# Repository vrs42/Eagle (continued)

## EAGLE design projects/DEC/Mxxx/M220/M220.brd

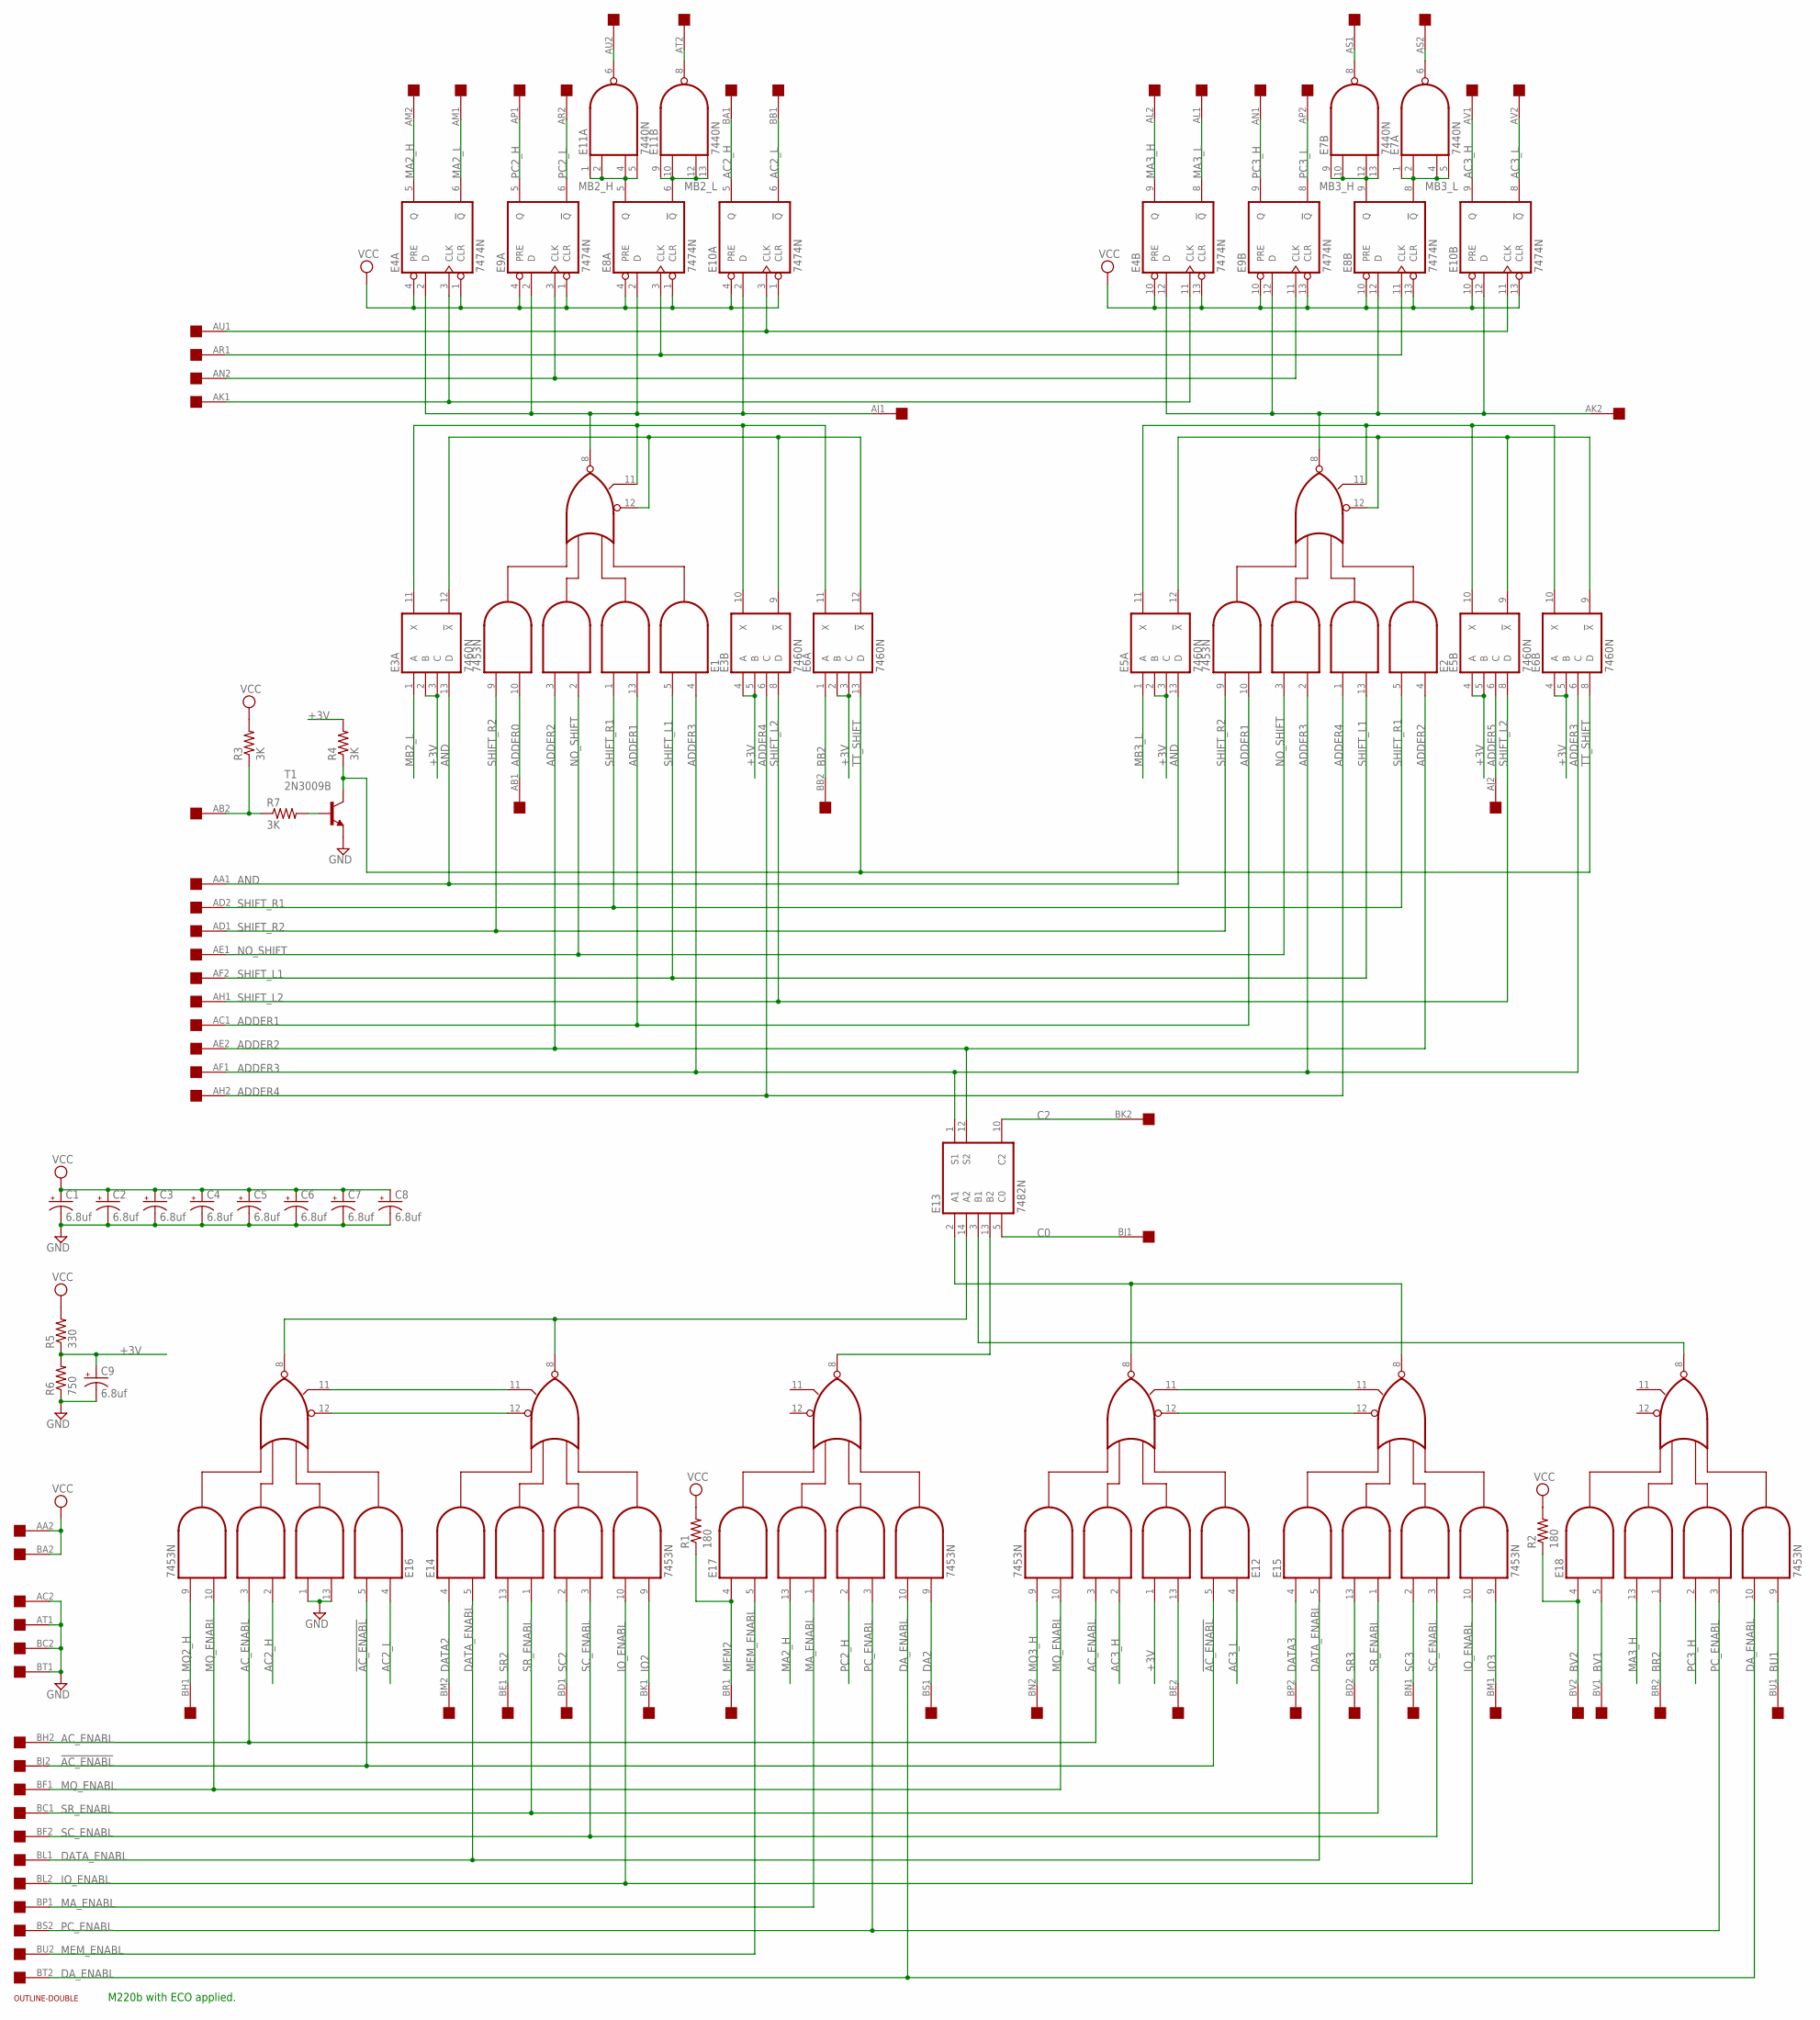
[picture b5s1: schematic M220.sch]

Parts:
C1, C2, C3, C4, C5, C6, C7, C8, C9: 6.8uf; E15-5
E1, E2, E12, E14, E15, E16, E17, E18: 7453N; DIL14
E3, E5, E6: 7460N; DIL14
E4, E8, E9, E10: 7474N; DIL14
E7, E11: 7440N; DIL14
E13: 7482N; DIL14
R1, R2: 180; 0207/10
R3, R4, R7: 3K; 0207/10
R5: 330; 0207/10
R6: 750; 0207/10
T1: 2N3009B; TO5
U$1: DOUBLE; EDGE-CON4
U$2: OUTLINE-DOUBLE; DOUBLE

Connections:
!AC_ENABL: E12.5 (I2), E16.5 (I2), U$1.BJ2
!TT_SHIFT: R3.1, R7.1, U$1.AB2
+3V: C9.+, E3.2 (B), E3.3 (C), E3.4 (A), E3.5 (B), E5.2 (B), E5.3 (C), E5.4 (A), E5.5 (B), E6.2 (B), E6.3 (C), E6.4 (A), E6.5 (B), E12.1 (I4), R4.2, R5.1, R6.2
AC2_H: E10.5 (Q), E16.2 (I5), U$1.BA1
AC2_L: E10.6 (!Q), E16.4 (I1), U$1.BB1
AC3_H: E10.9 (Q), E12.2 (I5), U$1.AV1
AC3_L: E10.8 (!Q), E12.4 (I1), U$1.AV2
AC_ENABL: E12.3 (I6), E16.3 (I6), U$1.BH2
ADDER0: E1.10 (I7), U$1.AB1
ADDER1: E1.13 (I3), E2.10 (I7), U$1.AC1
ADDER2: E1.3 (I6), E2.4 (I1), E13.12 (S2), U$1.AE2
ADDER3: E1.4 (I1), E2.2 (I5), E6.6 (C), E13.1 (S1), U$1.AF1
ADDER4: E2.1 (I4), E3.6 (C), U$1.AH2
ADDER5: E5.6 (C), U$1.AJ2
AJ1: E1.8 (O), E4.2 (D), E8.2 (D), E9.2 (D), E10.2 (D), U$1.AJ1
AK1: E4.3 (CLK), E4.11 (CLK), U$1.AK1
AK2: E2.8 (O), E4.12 (D), E8.12 (D), E9.12 (D), E10.12 (D), U$1.AK2
AN2: E9.3 (CLK), E9.11 (CLK), U$1.AN2
AND: E3.13 (D), E5.13 (D), U$1.AA1
AR1: E8.3 (CLK), E8.11 (CLK), U$1.AR1
AS1: E7.8 (O), U$1.AS1
AS2: E7.6 (O), U$1.AS2
AT2: E11.8 (O), U$1.AT2
AU1: E10.3 (CLK), E10.11 (CLK), U$1.AU1
AU2: E11.6 (O), U$1.AU2
BB2: E6.1 (A), U$1.BB2
BE2: E12.13 (I3), U$1.BE2
BR2: E18.1 (I4), U$1.BR2
BU1: E18.9 (I8), U$1.BU1
BV1: E18.5 (I2), U$1.BV1
BV2: E18.4 (I1), R2.1, U$1.BV2
C0: E13.5 (C0), U$1.BJ1
C2: E13.10 (C2), U$1.BK2
DA2: E17.9 (I8), U$1.BS1
DATA2: E14.4 (I1), U$1.BM2
DATA3: E15.4 (I1), U$1.BP2
DATA_ENABL: E14.5 (I2), E15.5 (I2), U$1.BL1
DA_ENABL: E17.10 (I7), E18.10 (I7), U$1.BT2
GND: C1.-, C2.-, C3.-, C4.-, C5.-, C6.-, C7.-, C8.-, C9.-, E1.7 (GND), E2.7 (GND), E3.7 (GND), E4.7 (GND), E5.7 (GND), E6.7 (GND), E7.7 (GND), E8.7 (GND), E9.7 (GND), E10.7 (GND), E11.7 (GND), E12.7 (GND), E13.11 (GND), E14.7 (GND), E15.7 (GND), E16.1 (I4), E16.7 (GND), E16.13 (I3), E17.7 (GND), E18.7 (GND), R6.1, T1.1 (E), U$1.AC2, U$1.AT1, U$1.BC2, U$1.BT1
IO2: E14.9 (I8), U$1.BK1
IO3: E15.9 (I8), U$1.BM1
IO_ENABL: E14.10 (I7), E15.10 (I7), U$1.BL2
MA2_H: E4.5 (Q), E17.13 (I3), U$1.AM2
MA2_L: E4.6 (!Q), U$1.AM1
MA3_H: E4.9 (Q), E18.13 (I3), U$1.AL2
MA3_L: E4.8 (!Q), U$1.AL1
MA_ENABL: E17.1 (I4), U$1.BP1
MB2_H: E8.5 (Q), E11.1 (I0), E11.2 (I1), E11.4 (I2), E11.5 (I3)
MB2_L: E3.1 (A), E8.6 (!Q), E11.9 (I0), E11.10 (I1), E11.12 (I2), E11.13 (I3)
MB3_H: E7.9 (I0), E7.10 (I1), E7.12 (I2), E7.13 (I3), E8.9 (Q)
MB3_L: E5.1 (A), E7.1 (I0), E7.2 (I1), E7.4 (I2), E7.5 (I3), E8.8 (!Q)
MEM2: E17.4 (I1), R1.1, U$1.BR1
MEM_ENABL: E17.5 (I2), U$1.BU2
MQ2_H: E16.9 (I8), U$1.BH1
MQ3_H: E12.9 (I8), U$1.BN2
MQ_ENABL: E12.10 (I7), E16.10 (I7), U$1.BF1
unnamed: E12.12 (I9), E15.12 (I9)
unnamed: R7.2, T1.2 (B)
unnamed: E12.11 (I10), E15.11 (I10)
unnamed: E13.14 (A2), E14.8 (O), E16.8 (O)
unnamed: E14.11 (I10), E16.11 (I10)
unnamed: E14.12 (I9), E16.12 (I9)
unnamed: E12.8 (O), E13.2 (A1), E15.8 (O)
unnamed: E2.12 (I9), E5.9 (!X), E5.12 (!X), E6.9 (!X)
unnamed: E1.12 (I9), E3.9 (!X), E3.12 (!X), E6.12 (!X)
unnamed: E2.11 (I10), E5.10 (X), E5.11 (X), E6.10 (X)
unnamed: E13.13 (B2), E17.8 (O)
unnamed: E1.11 (I10), E3.10 (X), E3.11 (X), E6.11 (X)
unnamed: E13.3 (B1), E18.8 (O)
NO_SHIFT: E1.2 (I5), E2.3 (I6), U$1.AE1
PC2_H: E9.5 (Q), E17.2 (I5), U$1.AP1
PC2_L: E9.6 (!Q), U$1.AR2
PC3_H: E9.9 (Q), E18.2 (I5), U$1.AN1
PC3_L: E9.8 (!Q), U$1.AP2
PC_ENABL: E17.3 (I6), E18.3 (I6), U$1.BS2
SC2: E14.2 (I5), U$1.BD1
SC3: E15.2 (I5), U$1.BN1
SC_ENABL: E14.3 (I6), E15.3 (I6), U$1.BF2
SHIFT_L1: E1.5 (I2), E2.13 (I3), U$1.AF2
SHIFT_L2: E3.8 (D), E5.8 (D), U$1.AH1
SHIFT_R1: E1.1 (I4), E2.5 (I2), U$1.AD2
SHIFT_R2: E1.9 (I8), E2.9 (I8), U$1.AD1
SR2: E14.13 (I3), U$1.BE1
SR3: E15.13 (I3), U$1.BD2
SR_ENABL: E14.1 (I4), E15.1 (I4), U$1.BC1
TT_SHIFT: E6.8 (D), E6.13 (D), R4.1, T1.3 (C)
VCC: C1.+, C2.+, C3.+, C4.+, C5.+, C6.+, C7.+, C8.+, E1.14 (VCC), E2.14 (VCC), E3.14 (VCC), E4.1 (CLR), E4.4 (PRE), E4.10 (PRE), E4.13 (CLR), E4.14 (VCC), E5.14 (VCC), E6.14 (VCC), E7.14 (VCC), E8.1 (CLR), E8.4 (PRE), E8.10 (PRE), E8.13 (CLR), E8.14 (VCC), E9.1 (CLR), E9.4 (PRE), E9.10 (PRE), E9.13 (CLR), E9.14 (VCC), E10.1 (CLR), E10.4 (PRE), E10.10 (PRE), E10.13 (CLR), E10.14 (VCC), E11.14 (VCC), E12.14 (VCC), E13.4 (VCC), E14.14 (VCC), E15.14 (VCC), E16.14 (VCC), E17.14 (VCC), E18.14 (VCC), R1.2, R2.2, R3.2, R5.2, U$1.AA2, U$1.BA2

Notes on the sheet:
M220b with ECO applied.

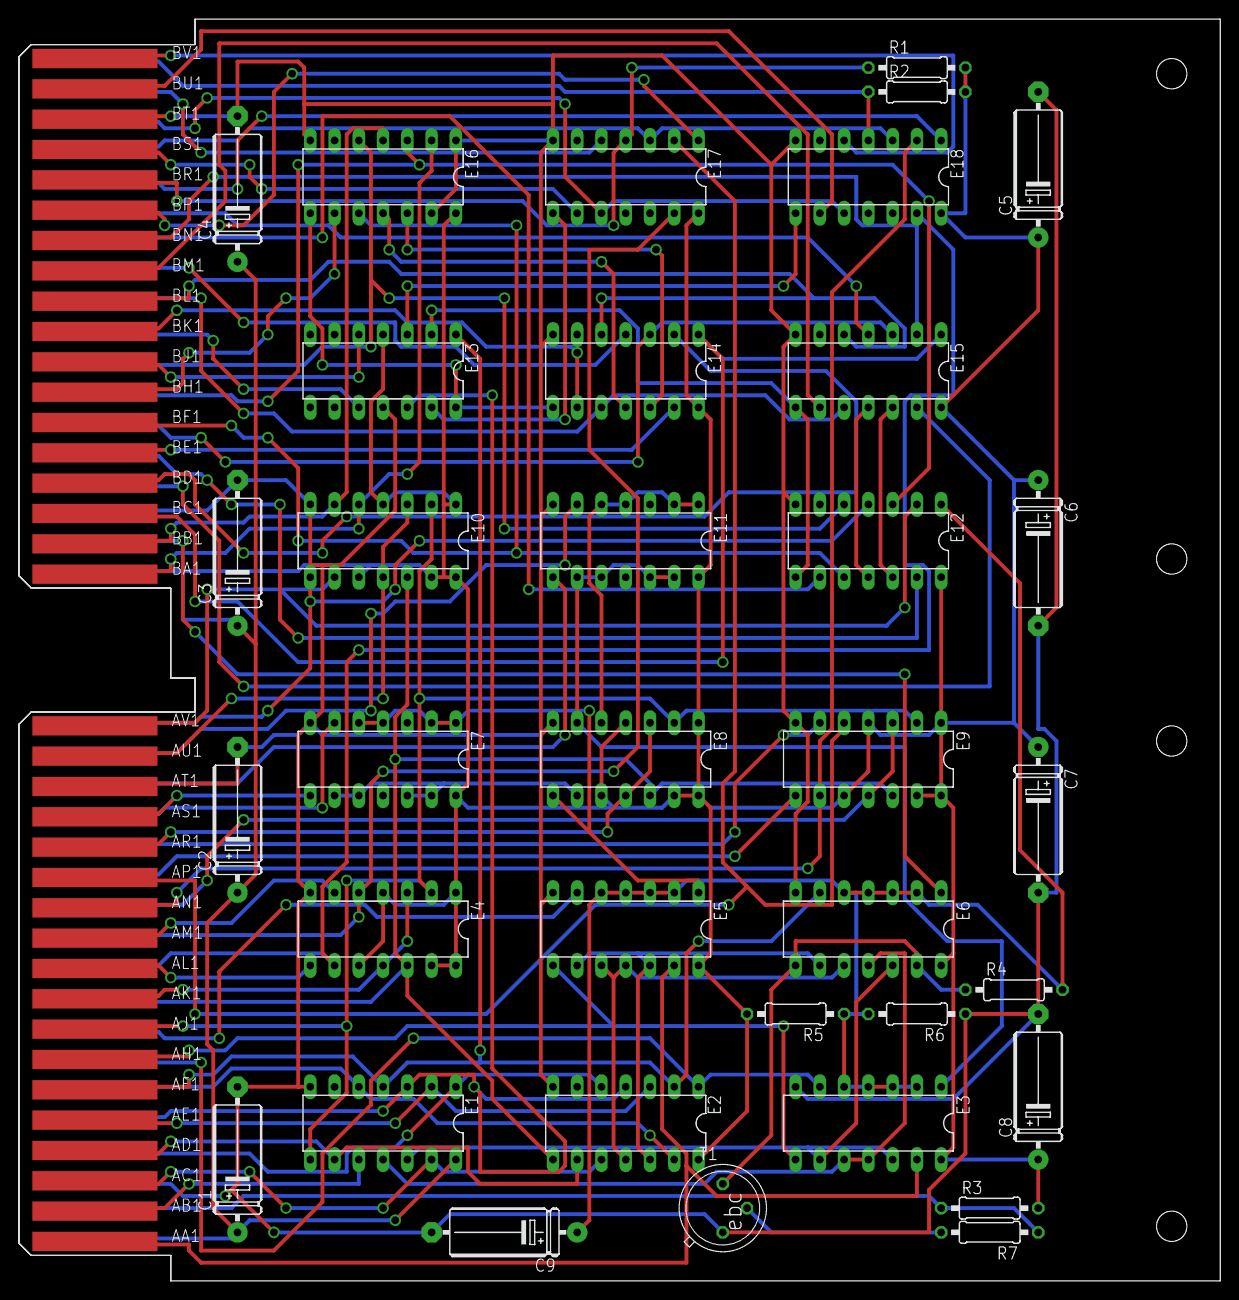
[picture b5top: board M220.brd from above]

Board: 2 copper layers, 125.7 x 132.1 mm, 37 parts (0 on the bottom side), 87 nets.

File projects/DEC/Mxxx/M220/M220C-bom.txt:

Partlist exported from C:/Users/Vince/Documents/Eagle/projects/DEC/Mxxx/M220/M220C.sch at 12/9/2017 4:49:37 PM

Qty Value          Device            Package   Parts                                Description                                                     
1                  DOUBLE            EDGE-CON4 U$1                                  Double-Height DEC board                                         
2   180            R-US_0207/10      0207/10   R1, R2                               RESISTOR, American symbol                                       
1   2N3009B        2N1613            TO5       T1                                   NPN TRANSISTOR                                                  
1   330            R-US_0207/10      0207/10   R6                                   RESISTOR, American symbol                                       
3   3K             R-US_0207/10      0207/10   R3, R4, R5                           RESISTOR, American symbol                                       
9   6.8uf          CPOL-USE15-5AXIAL E15-5     C1, C2, C3, C4, C5, C6, C7, C8, C9   0.6" veresion of an electrolytic                                
2   7440N          74S20N            DIL14     E7, E11                              Dual 4-input NAND gate                                          
8   7453N          7453N             DIL14     E1, E2, E12, E14, E15, E16, E17, E18 4-2-3-2 input AND OR INVERTER gates                             
3   7460N          7460N             DIL14     E3, E5, E6                           Dual 4-input EXPANDER                                           
4   7474N          74S74N            DIL14     E4, E8, E9, E10                      Dual D type positive edge triggered FLIP FLOP, preset and clear 
1   7482N          7482N             DIL14     E13                                  2-bit binary full ADDER                                         
1   750            R-US_0207/10      0207/10   R7                                   RESISTOR, American symbol                                       
1   OUTLINE-DOUBLE OUTLINE-DOUBLE    DOUBLE    U$2                                  Board outlines for DEC boards.
